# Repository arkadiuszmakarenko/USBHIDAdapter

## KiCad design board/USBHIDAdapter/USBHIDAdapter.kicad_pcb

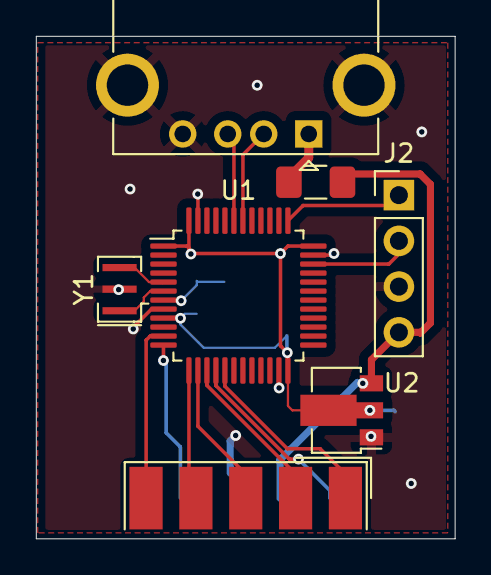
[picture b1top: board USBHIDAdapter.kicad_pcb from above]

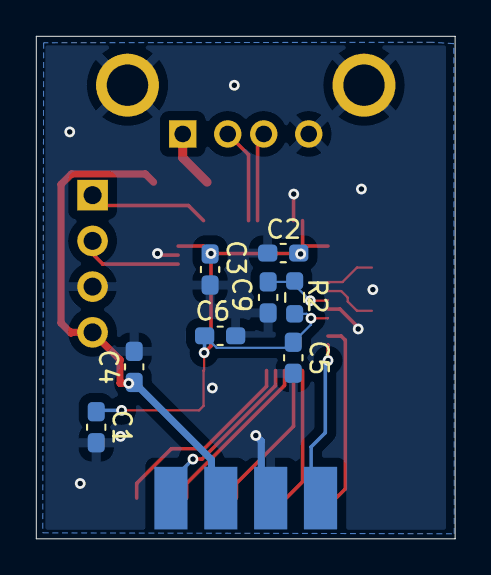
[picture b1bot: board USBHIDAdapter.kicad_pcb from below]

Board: 2 copper layers, 23.3 x 27.9 mm, 15 parts (8 on the bottom side), 18 nets.

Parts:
C1, C2, C3, C4, C5, C6: C; C_0603_1608Metric_Pad1.08x0.95mm_HandSolder
C9: 0.1μF; C_0603_1608Metric_Pad1.08x0.95mm_HandSolder
F1: Fuse; Fuse_1206_3216Metric_Pad1.42x1.75mm_HandSolder
J1: DE9_Plug; DSUB-9_Female_EdgeMount_P2.77mm
J2: Conn_01x04; PinHeader_1x04_P2.54mm_Vertical
J3: USB_1; USB_A_CONNFLY_DS1095-WNR0
R2: R; R_0603_1608Metric_Pad0.98x0.95mm_HandSolder
U1: CH32V203C8T6-CH32V103C; CH32V203C8T6_LQFP-48_7x7mm_P0.5mm
U2: LM1117MP-3.3; SOT-89-3
Y1: Resonator; Resonator_SMD_Murata_CSTxExxV-3Pin_3.0x1.1mm

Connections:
+3.3V: C1.1, C2.1, C3.1, C5.1, C6.1, R2.1, U1.1 (VBAT), U1.9 (VDDA), U1.24 (VDD_VIO1), U1.36 (VDD_2), U1.48 (VDD_VIO_3), U2.2 (VO)
+5V: C4.1, F1.2, J1.7, J2.4, U2.3 (VI)
/NRST: C9.1, R2.2, U1.7 (NRST)
/OSC_IN: U1.5 (OSC_IN_PD0), Y1.3
/OSC_OUT: U1.6 (OSC_OUT_PD1), Y1.1
/PIN1: J1.1, U1.17 (PA7_ADC7)
/PIN2: J1.2, U1.15 (PA5_ADC5)
/PIN3: J1.3, U1.14 (PA4_ADC4)
/PIN4: J1.4, U1.13 (PA3_ADC3)
/PIN5: J1.5, U1.11 (PA1_ADC1)
/PIN6: J1.6, U1.16 (PA6_ADC6)
/PIN9: J1.9, U1.12 (PA2_ADC2)
/SWCLK: J2.1, U1.37 (PA14_SWCLK)
/SWDIO: J2.2, U1.34 (PA13_SWDIO)
/USB_DM: J3.2 (D-), U1.42 (PB6_USB2DM)
/USB_DP: J3.3 (D+), U1.43 (PB7_USB2DP)
GND: C1.2, C2.2, C3.2, C4.2, C5.2, C6.2, C9.2, J1.8, J2.3, J3.4 (GND), J3.5 (Shield), U1.8 (VSSA), U1.23 (VSS1), U1.35 (VSS_2), U1.47 (VSS_3), U2.1 (GND), Y1.2
unnamed: F1.1, J3.1 (VBUS)

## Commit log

2024-04-13 Source code, board and gerbers
2024-04-28 Firmware adapted to new pins
